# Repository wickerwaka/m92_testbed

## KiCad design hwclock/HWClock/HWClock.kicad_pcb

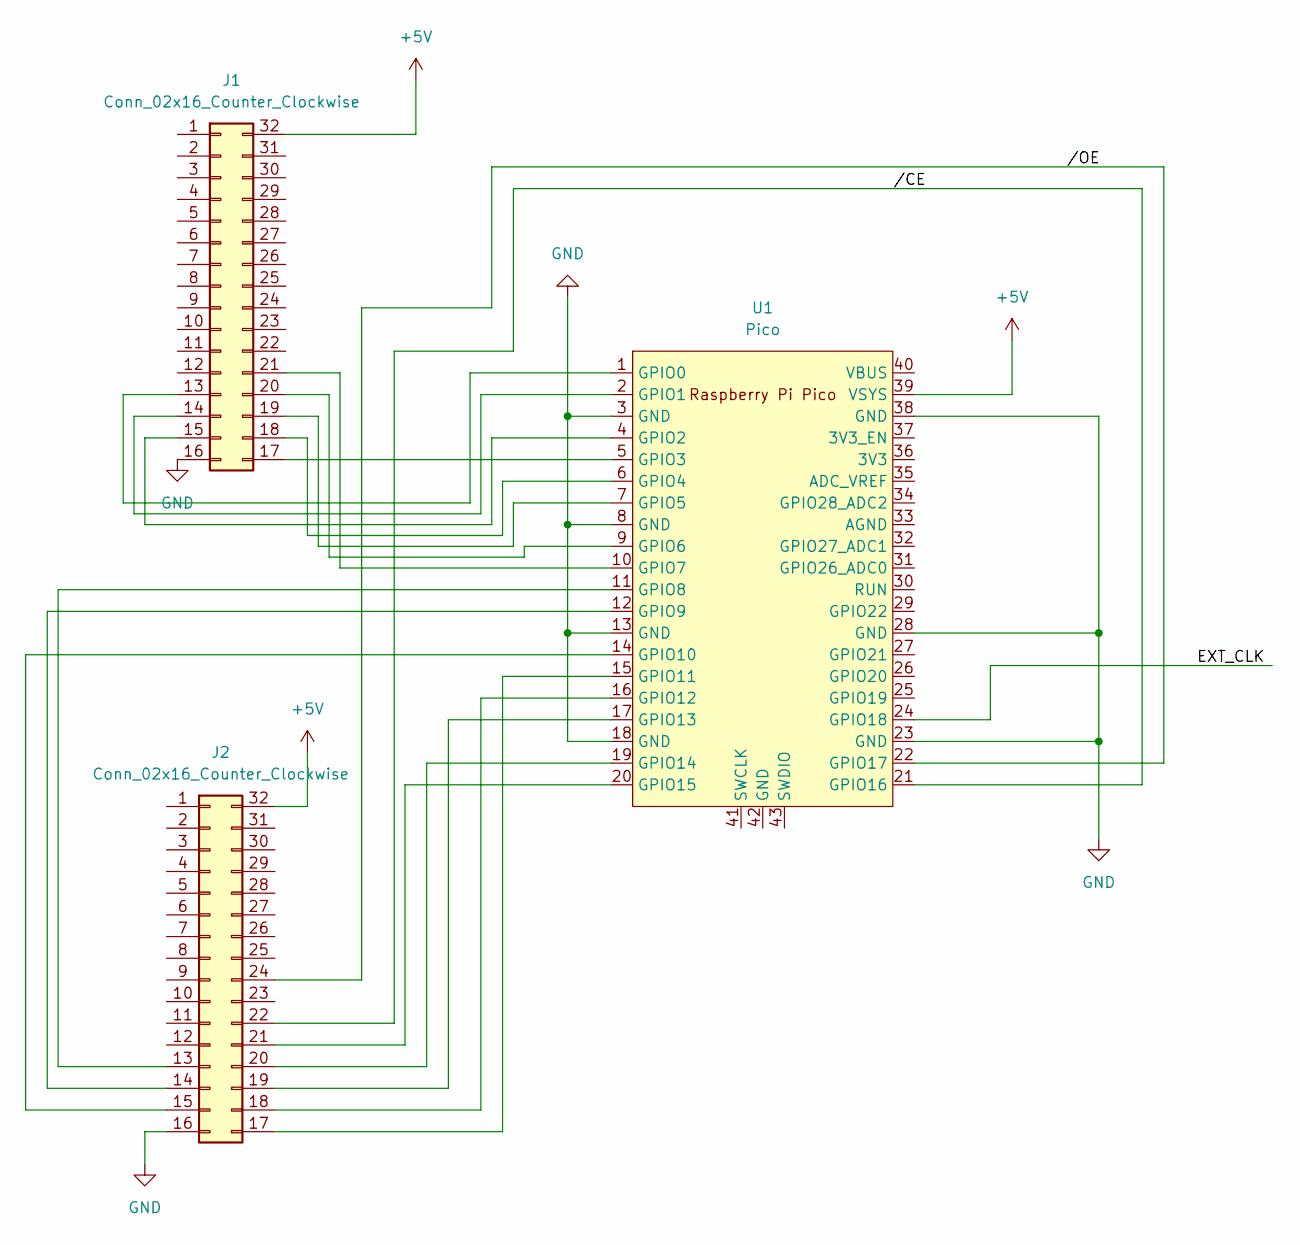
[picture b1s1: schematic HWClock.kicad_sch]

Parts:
J1, J2: Conn_02x16_Counter_Clockwise; DIP-32_W15.24mm
U1: Pico; RPi_Pico_SMD_TH

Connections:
+5V: J1.32, J2.32, U1.39 (VSYS)
/EXT_CLK: U1.24 (GPIO18)
//CE: J2.22, U1.21 (GPIO16)
//OE: J2.24, U1.22 (GPIO17)
GND: J1.16, J2.16, U1.3 (GND), U1.8 (GND), U1.13 (GND), U1.18 (GND), U1.23 (GND), U1.28 (GND), U1.38 (GND)
unnamed: J1.13, U1.1 (GPIO0)
unnamed: J1.14, U1.2 (GPIO1)
unnamed: J1.15, U1.4 (GPIO2)
unnamed: J1.17, U1.5 (GPIO3)
unnamed: J1.18, U1.6 (GPIO4)
unnamed: J1.19, U1.7 (GPIO5)
unnamed: J1.20, U1.9 (GPIO6)
unnamed: J1.21, U1.10 (GPIO7)
unnamed: J2.13, U1.11 (GPIO8)
unnamed: J2.14, U1.12 (GPIO9)
unnamed: J2.15, U1.14 (GPIO10)
unnamed: J2.17, U1.15 (GPIO11)
unnamed: J2.18, U1.16 (GPIO12)
unnamed: J2.19, U1.17 (GPIO13)
unnamed: J2.20, U1.19 (GPIO14)
unnamed: J2.21, U1.20 (GPIO15)

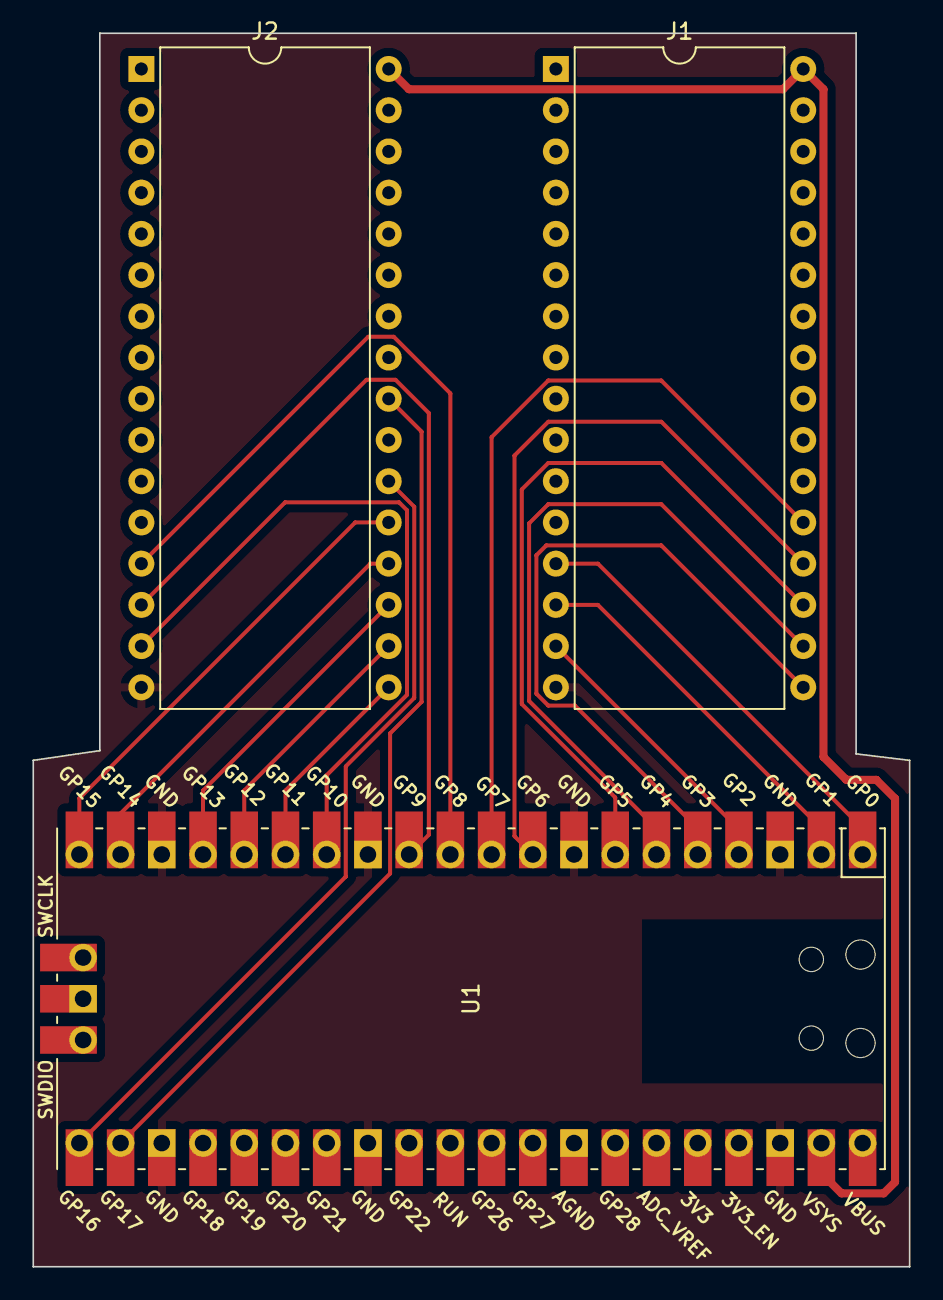
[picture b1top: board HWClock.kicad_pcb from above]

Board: 2 copper layers, 54.0 x 76.0 mm, 3 parts (0 on the bottom side), 20 nets.

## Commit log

2023-05-29 Some working C code
2023-06-13 Mark vector array as used
2023-07-11 Improve splitrom
2023-07-12 picorom support
2023-07-20 Comms via python
2023-07-21 Adapt F2 testrom to M92 and ia16 compiler
2023-07-22 Basic information display
2023-08-03 Clear vram
2023-08-04 All basic functionality working on m90
2023-08-12 stuff
2023-11-28 Basic m107 update and running
2024-02-09 Tests for new v33 core
2024-02-10 more tests
2024-02-10 simplified main loop for testing
2024-02-11 Add rtypeleo
2024-02-22 timing tests
2024-02-26 Remove need to 4 roms
2024-02-27 Use the audio cpu to generate timer data
2024-02-27 some initial timing tests
2024-02-29 Mister support Adding timing tests
2024-03-02 Multipage timing tests
2024-03-06 Use hardware timer for tests
2024-03-06 nop_fetching test
2024-03-07 Add DS_Store to gitignore
2024-03-07 HW timer firmware and pcb
2024-03-07 Remove lock tests
2024-03-09 Switch clk pin
2024-03-09 Lock timing
2024-03-18 Makefile support for tests
2024-05-04 m107 updates
2024-05-04 move playfield code to separate file
2024-05-24 Various updates to test cases
2024-08-10 Add reset
2024-08-22 Port playfield from m107 Automatically deploy to picorom on save
2024-10-14 Tweaks
2024-10-14 Test MRA creation
2024-10-18 Fixes to make things work on basic mister core
